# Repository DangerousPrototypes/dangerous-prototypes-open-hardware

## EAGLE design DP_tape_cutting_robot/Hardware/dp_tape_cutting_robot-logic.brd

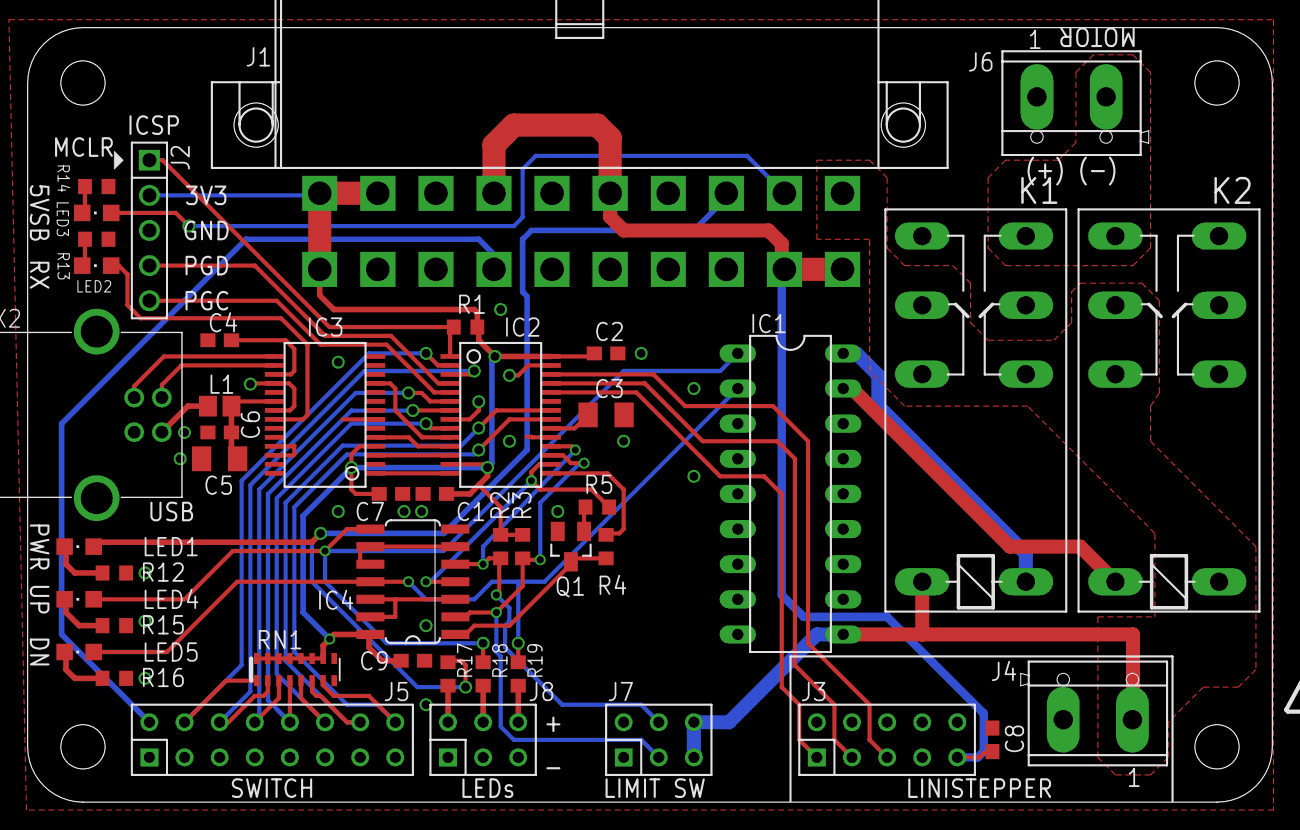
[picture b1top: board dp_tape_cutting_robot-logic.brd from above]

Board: 2 copper layers, 90.0 x 56.0 mm, 48 parts (1 on the bottom side), 53 nets.

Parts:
C1, C2, C4, C6, C7, C8, C9: 100nF; C603
C3, C5: 10uF 16V; SMC_A
IC1: DIL18
IC2: IC_UC_PIC24FJ64GA002; SSOP-28
IC3: IC_FT232RL; SSOP-28
IC4: 74LV00; SO14
J1: CON_ATX_PWR-90DEG; CON_ATX_PWR_90DEG
J2: CON_HEADER_PRG_PIC_ICSP0.1INCH_A; HEADER_PRG_1X05
J3: CON_HEADER_2X05-PTH; M2X5
J4, J6: CON_TERMINAL_BLOCK_02-5MM; TERMINAL_BLOCK_2P_5
J5: CON_HEADER_2X08; M2X8
J7, J8: CON_HEADER_2X03-PTH; M2X3
K1, K2: G2R2
L1: 700mA; FB805
LED1, LED2, LED3, LED4, LED5: LED-805
PCB2: PCB_DP_RECTANGLE-56X90; DP9056_V1
Q1: BC818; SOT-23
R1, R18, R19: R603
R2, R3, R12, R14, R17: 10K; R603
R4: 1K; R603
R5: 1.1K; R603
R13, R15, R16: 1K1; R603
RN1: 10K-8; CAT16-F8/CAT16-J8
U$1: FRAME_DINA4_L; DP_LOGO
U$3: DP_LOGO_ART_0.5X0.5
X2: MINI-USB_4P-85-32004-10X; 85-32004-10X

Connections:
5VSB: J1.9, LED3.A
+3V3: C1.1, C2.2, C7.2, C9.2, IC2.13, IC2.28, IC3.4, IC4.14, J1.1, J1.2, J1.11, J2.2, R1.2, R2.2, R3.2, RN1.10, RN1.11, RN1.12, RN1.13, RN1.14, RN1.15, RN1.16
+5V: C8.2, J1.4, J1.6, J1.19, J1.20, J3.9
+12V: IC1.10, J1.10, J4.1, J7.5, J7.6, K1.2, K1.P1, K2.1, K2.P1
B_BACK: IC2.21, J5.16, RN1.7
B_DOWN: IC2.7, J5.10, RN1.4
B_FORWARD: IC2.22, J5.14, RN1.6
B_MANUAL: IC2.6, J5.8, RN1.3
B_START: IC2.2, J5.4, RN1.1
B_STOP: IC2.3, J5.6, RN1.2
B_UP: IC2.9, J5.12, RN1.5
CTRL_DN: IC2.15, R4.1
CTRL_UP: IC2.16, IC4.4, R5.1
CTS: IC2.10, IC3.11
DIR: IC2.25, J3.3
ENA: IC2.24, J3.1
GND: C1.2, C2.1, C3.-, C4.1, C5.-, C6.1, C7.1, C8.1, C9.1, IC1.9, IC2.8, IC2.19, IC2.27, IC3.7, IC3.18, IC3.21, IC3.25, IC3.26, IC4.7, J1.3, J1.5, J1.7, J1.13, J1.15, J1.16, J1.17, J2.3, J3.2, J3.4, J3.6, J3.7, J3.8, J3.10, J4.2, J5.1, J5.3, J5.5, J5.7, J5.9, J5.11, J5.13, J5.15, J7.1, J7.2, J8.1, J8.3, J8.5, K1.P2, K2.P2, Q1.2, R12.1, R13.1, R14.1, R15.1, R16.1, X2.4
ICSP_MCLR: IC2.1, J2.1, R1.1
ICSP_PGC: IC2.5, J2.5
ICSP_PGD: IC2.4, J2.4
LED_RX: IC3.22, LED2.A
MOTOR+: J6.1, K1.S1, K2.S2
MOTOR-: J6.2, K1.S2, K2.S1
MOTOR_DN: IC1.2, IC4.11, LED5.A, R19.1
MOTOR_UP: IC1.1, IC4.8, LED4.A, R18.1
unnamed: C3.+, IC2.20
unnamed: IC1.17, K2.2
unnamed: IC4.3, IC4.12, IC4.13
unnamed: LED1.C, R12.2
unnamed: IC4.1, Q1.3, R4.2
unnamed: Q1.1, R5.2
unnamed: LED2.C, R13.2
unnamed: C4.2, IC3.17
unnamed: LED3.C, R14.2
unnamed: LED4.C, R15.2
unnamed: LED5.C, R16.2
unnamed: IC1.18, K1.1
unnamed: IC3.16, X2.2
unnamed: IC3.15, X2.3
unnamed: C5.+, C6.2, IC3.20, L1.2
unnamed: L1.1, X2.1
unnamed: IC4.6, IC4.9, IC4.10
unnamed: J8.2, R17.2
unnamed: J8.4, R18.2
unnamed: J8.6, R19.2
PWR_GOOD: J1.8, LED1.A, R17.1
PWR_ON: J1.14, J5.2
RTS: IC2.12, IC3.3
RX: IC2.11, IC3.5
STP: IC2.26, J3.5
SW_DN: IC2.17, IC4.2, J7.3, R3.1
SW_UP: IC2.18, IC4.5, J7.4, R2.1
TX: IC2.14, IC3.1

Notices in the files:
DP_tape_cutting_robot/Hardware/dp_tape_cutting_robot-logic.brd:
LICENSE: CC-BY-SA
